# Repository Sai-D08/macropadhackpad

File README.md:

# macropadhackpad

Helo people, this is my first time making pcb's, I really enjoyed making it and hope this will be worthwhile and learnt a lot of things about electronics.
Thanks HACKCLUB!!!

# Schematic:

# PCB:

# CAD:

# BOM:

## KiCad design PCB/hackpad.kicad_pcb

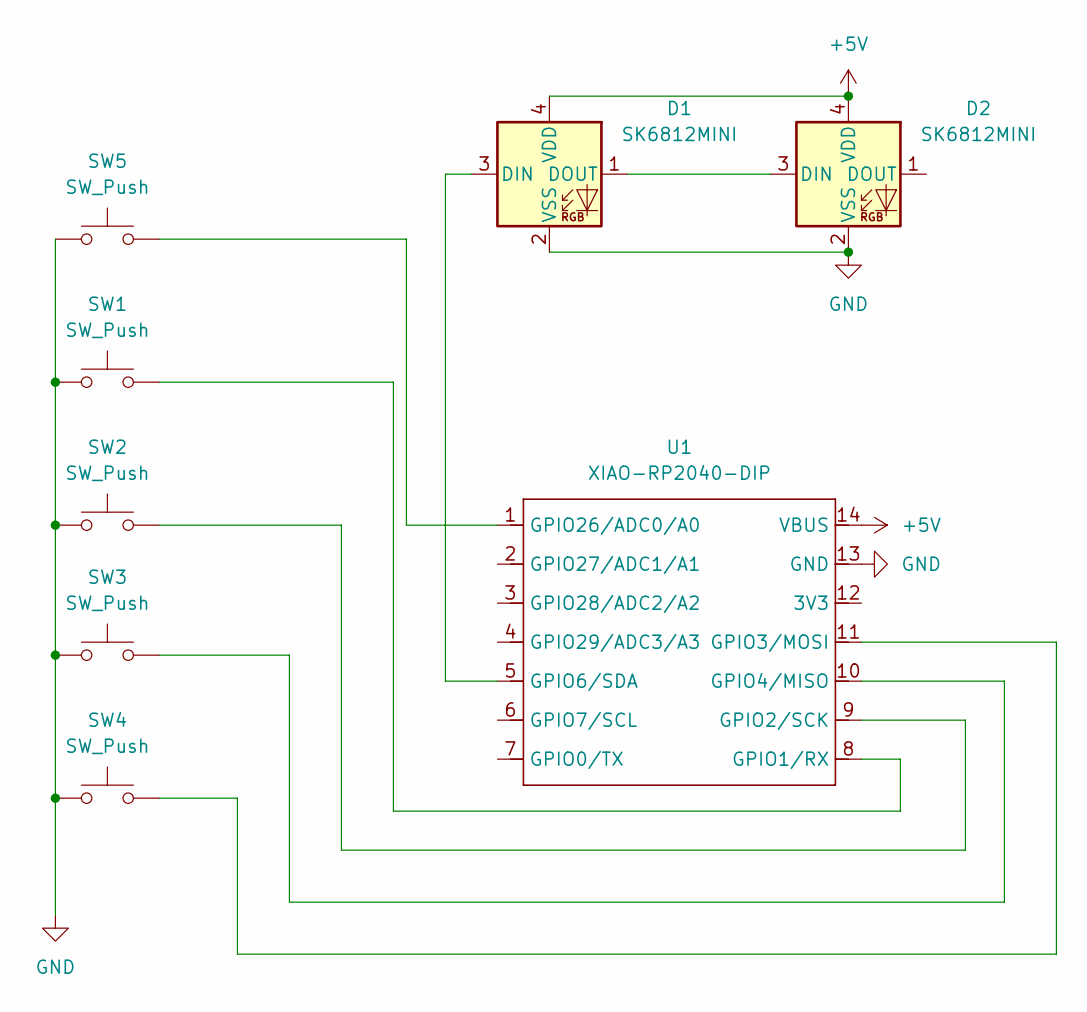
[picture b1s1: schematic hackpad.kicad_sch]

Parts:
D1, D2: SK6812MINI; LED_SK6812MINI_PLCC4_3.5x3.5mm_P1.75mm
SW1, SW2, SW3, SW4, SW5: SW_Push; SW_Cherry_MX_1.00u_PCB
U1: XIAO-RP2040-DIP

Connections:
+5V: D1.4 (VDD), D2.4 (VDD), U1.14 (VBUS)
GND: D1.2 (VSS), D2.2 (VSS), SW1.1, SW2.1, SW3.1, SW4.1, SW5.1, U1.13 (GND)
unnamed: D1.3 (DIN), U1.5 (GPIO6/SDA)
unnamed: D1.1 (DOUT), D2.3 (DIN)
unnamed: SW1.2, U1.8 (GPIO1/RX)
unnamed: SW2.2, U1.9 (GPIO2/SCK)
unnamed: SW4.2, U1.11 (GPIO3/MOSI)
unnamed: SW3.2, U1.10 (GPIO4/MISO)
unnamed: SW5.2, U1.1 (GPIO26/ADC0/A0)

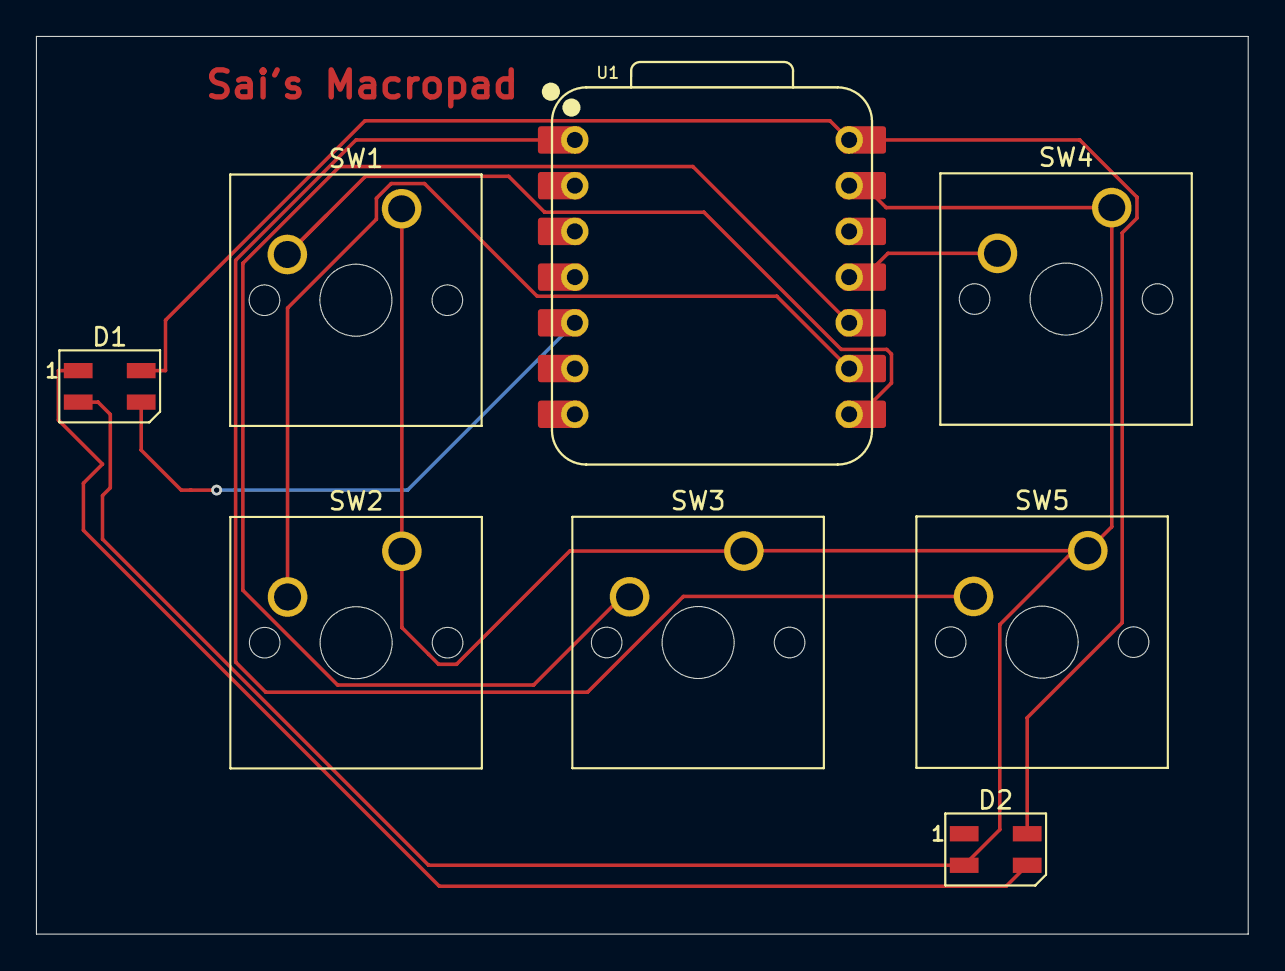
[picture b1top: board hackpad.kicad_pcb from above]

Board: 2 copper layers, 67.3 x 49.9 mm, 8 parts (0 on the bottom side), 9 nets.

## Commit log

2025-06-19 Create TEST
2025-06-19 GERBER Files
